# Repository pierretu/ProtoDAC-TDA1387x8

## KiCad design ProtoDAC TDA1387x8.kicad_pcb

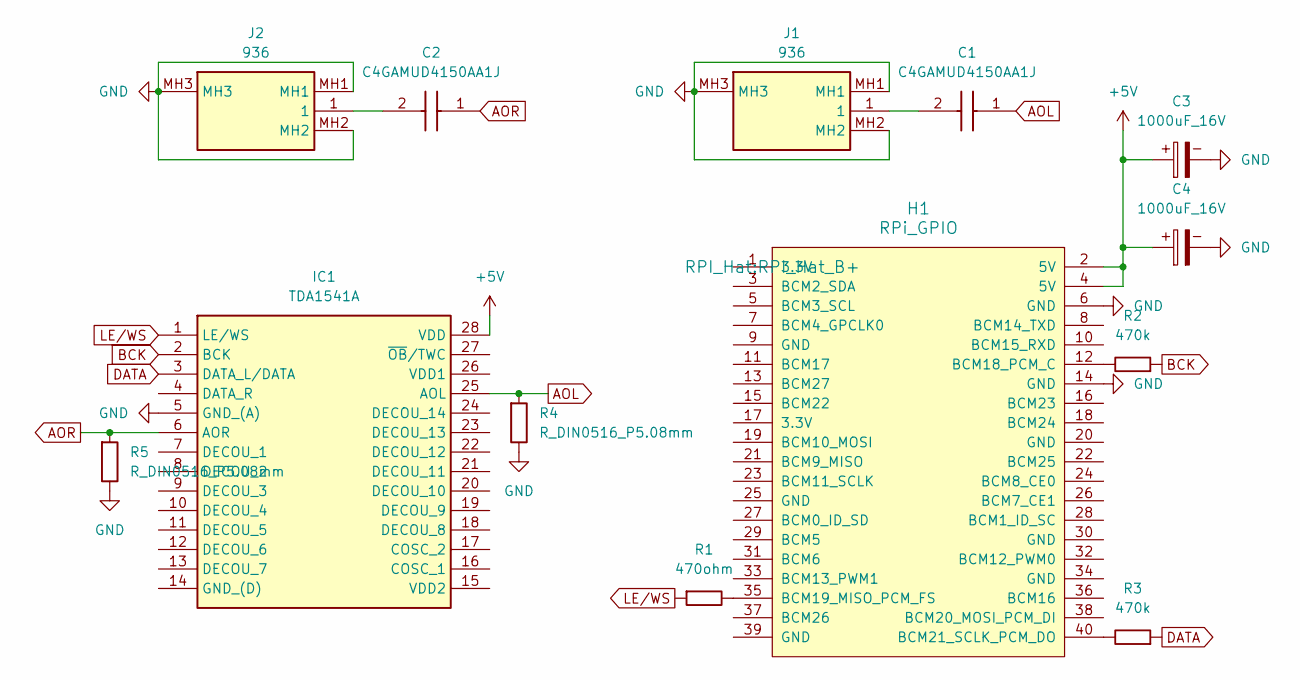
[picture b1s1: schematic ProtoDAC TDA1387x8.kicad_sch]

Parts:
C1, C2: C4GAMUD4150AA1J; CAPPA14200W120L4400D2450; Manufacturer_Part_Number C4GAMUD4150AA1J
C3, C4: 1000uF_16V; CP_Radial_D10.0mm_P5.00mm
H1: RPi_GPIO; RPI_Hat_B+
IC1: TDA1541A; DIP1652W53P254L3550H510Q28N; Manufacturer_Part_Number TDA1541A
J1, J2: 936; Manufacturer_Part_Number 936
R1: 470ohm; R_Axial_DIN0207_L6.3mm_D2.5mm_P10.16mm_Horizontal
R2, R3: 470k; R_Axial_DIN0207_L6.3mm_D2.5mm_P10.16mm_Horizontal
R4, R5: R_DIN0516_P5.08mm; R_Axial_DIN0516_L15.5mm_D5.0mm_P5.08mm_Vertical

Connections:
+5V: C3.1, C4.1, H1.2 (5V), H1.4 (5V), IC1.28 (VDD)
AOL: C1.1 (+), IC1.25 (AOL), R4.1
AOR: C2.1 (+), IC1.6 (AOR), R5.1
BCK: IC1.2 (BCK), R2.1
DATA: IC1.3 (DATA_L/DATA), R3.1
GND: C3.2, C4.2, H1.6 (GND), H1.14 (GND), IC1.5 (GND_(A)), J1.MH1, J1.MH2, J1.MH3, J2.MH1, J2.MH2, J2.MH3, R4.2, R5.2
LE/WS: IC1.1 (LE/WS), R1.1
unnamed: C1.2 (-), J1.1
unnamed: C2.2 (-), J2.1
unnamed: H1.12 (BCM18_PCM_C), R2.2
unnamed: H1.35 (BCM19_MISO_PCM_FS), R1.2
unnamed: H1.40 (BCM21_SCLK_PCM_DO), R3.2

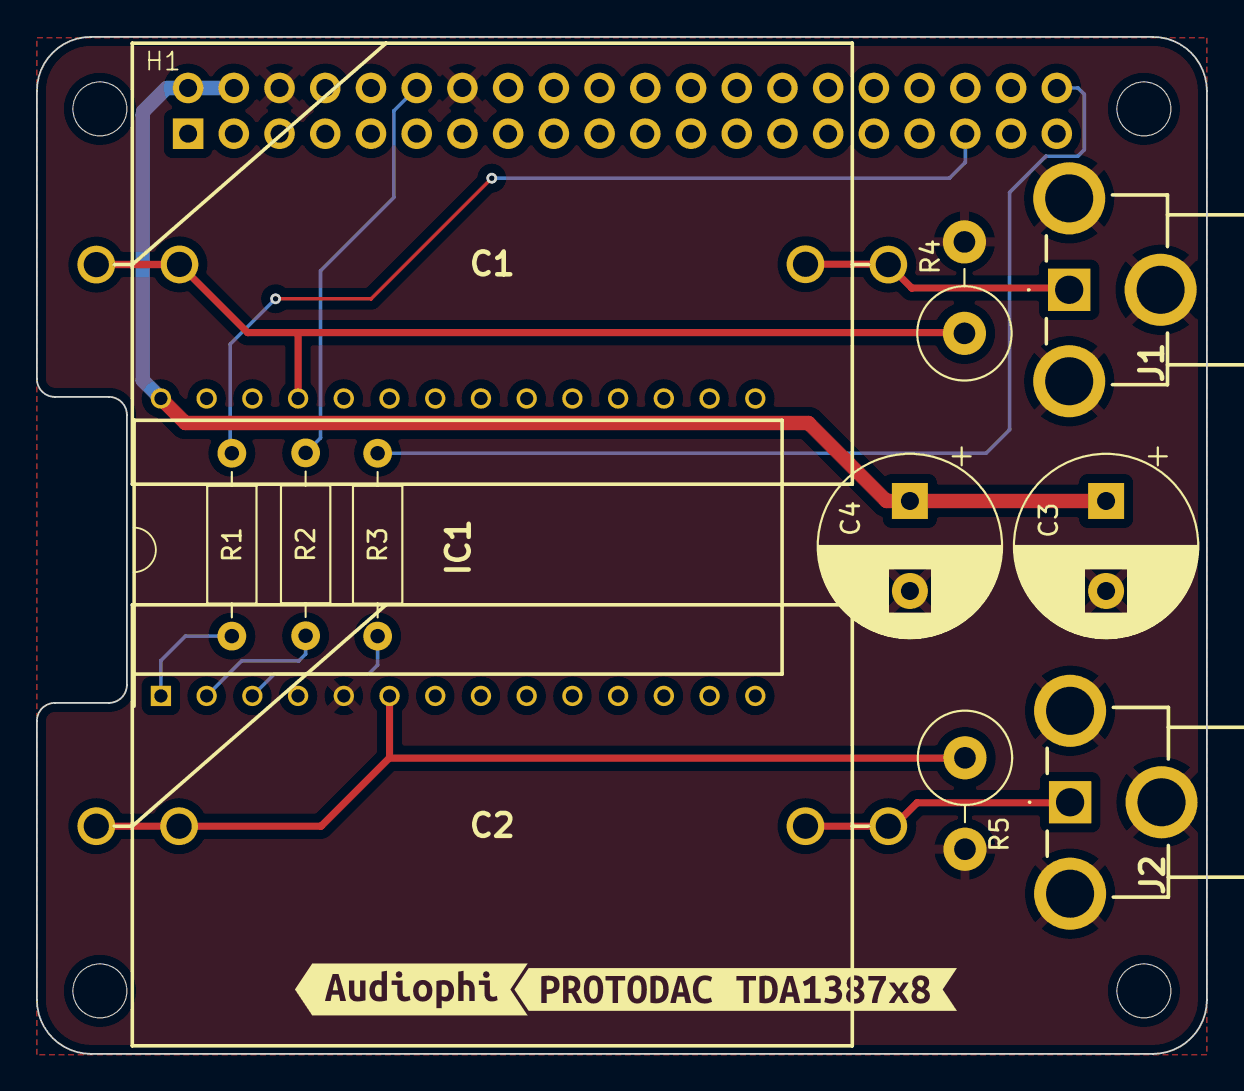
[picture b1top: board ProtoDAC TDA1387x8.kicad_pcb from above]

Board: 2 copper layers, 65.0 x 56.5 mm, 15 parts (0 on the bottom side), 12 nets.

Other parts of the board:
kibuzzard-674DA88C: G***; kibuzzard-674DA88C
kibuzzard-674DA90A: G***; kibuzzard-674DA90A

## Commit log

2024-11-10 Initial release
2024-12-02 Updated board to match new layout
